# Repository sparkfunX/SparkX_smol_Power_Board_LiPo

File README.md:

# SparkX smôl Power Board : LiPo

[*SparkX smôl Power Board : LiPo (SPX-18622)*](https://www.sparkfun.com/products/18622)

A power board for smôl:
- LiPo battery connector and charger
- Fuel gauge
- ATtiny841 for intelligent power management

## Repository Contents

- **/Documentation** - Datasheets etc.
- **/Hardware** - Eagle design files
- **LICENSE.md** contains the licence information

## Product Versions

- [SPX-18622](https://www.sparkfun.com/products/18622) - Original SparkX Release.

## License Information

This product is _**open source**_!

Please review the LICENSE.md file for license information.

If you have any questions or concerns on licensing, please contact technical support on our [SparkFun forums](https://forum.sparkfun.com/viewforum.php?f=123).

Distributed as-is; no warranty is given.

- Your friends at SparkFun.

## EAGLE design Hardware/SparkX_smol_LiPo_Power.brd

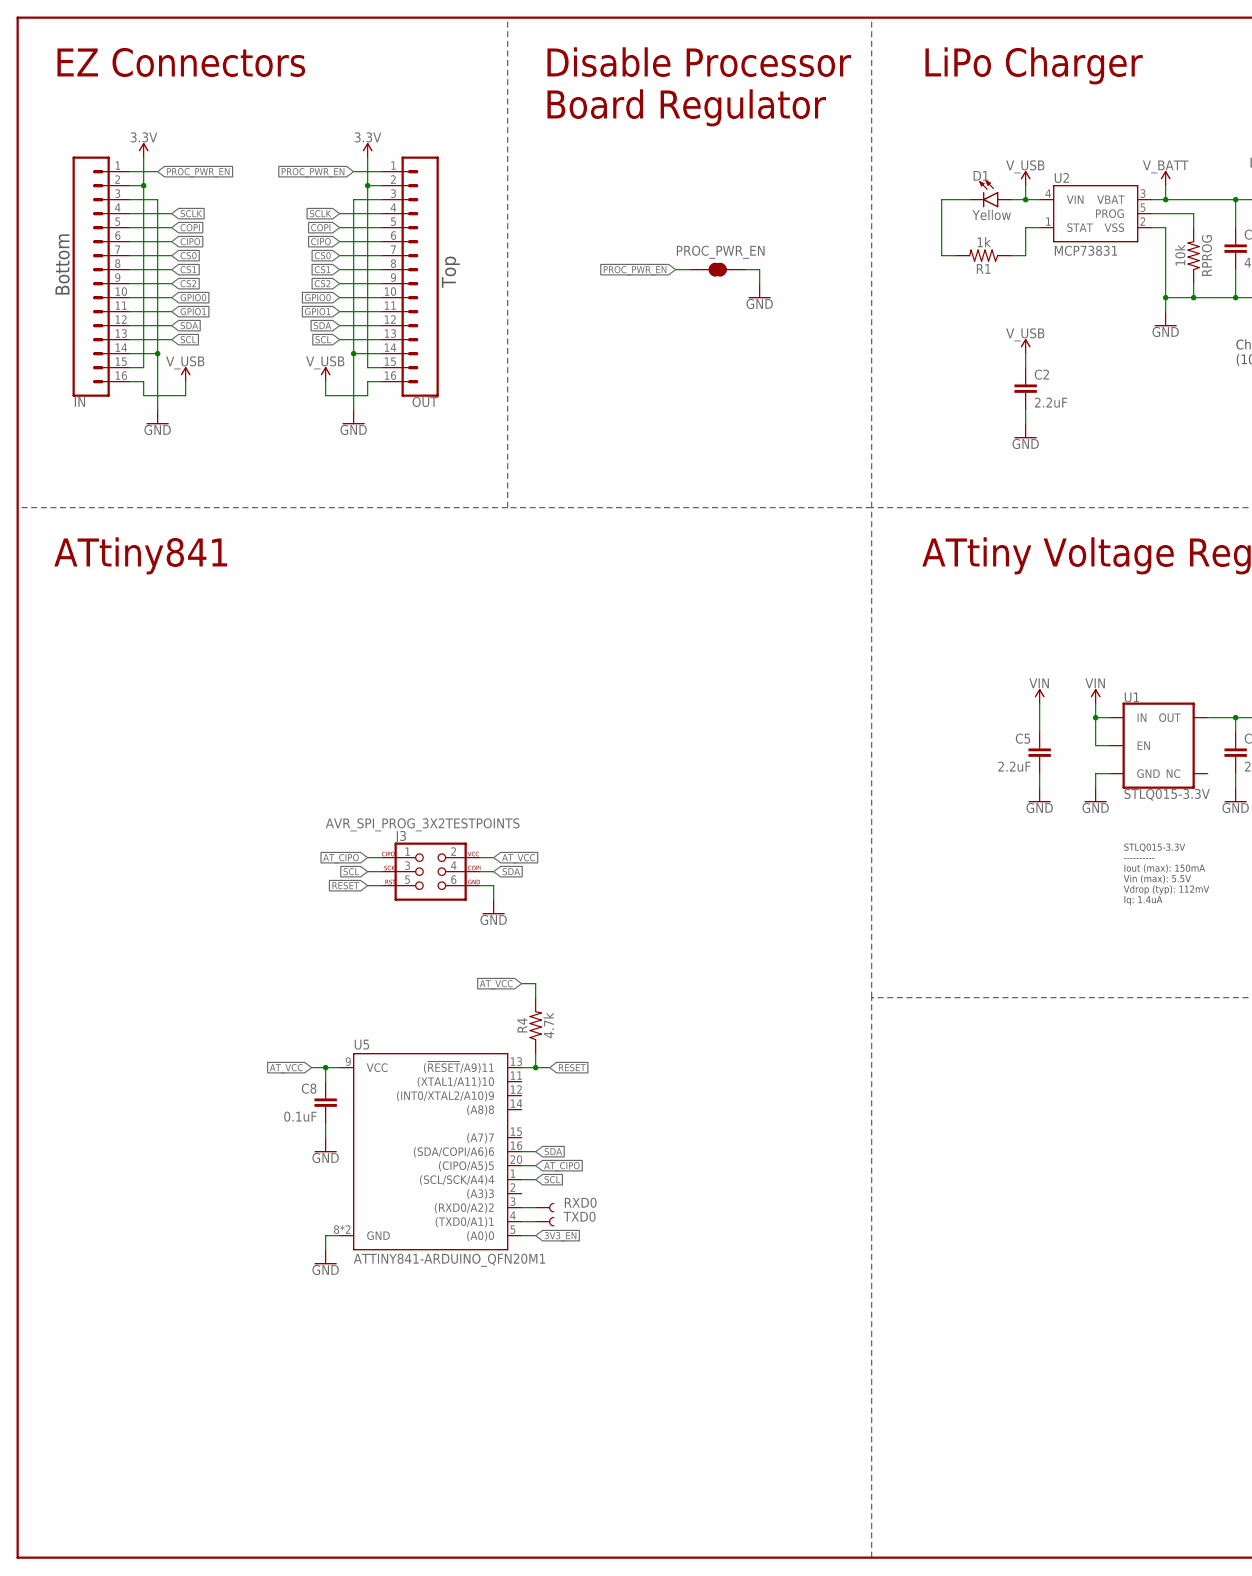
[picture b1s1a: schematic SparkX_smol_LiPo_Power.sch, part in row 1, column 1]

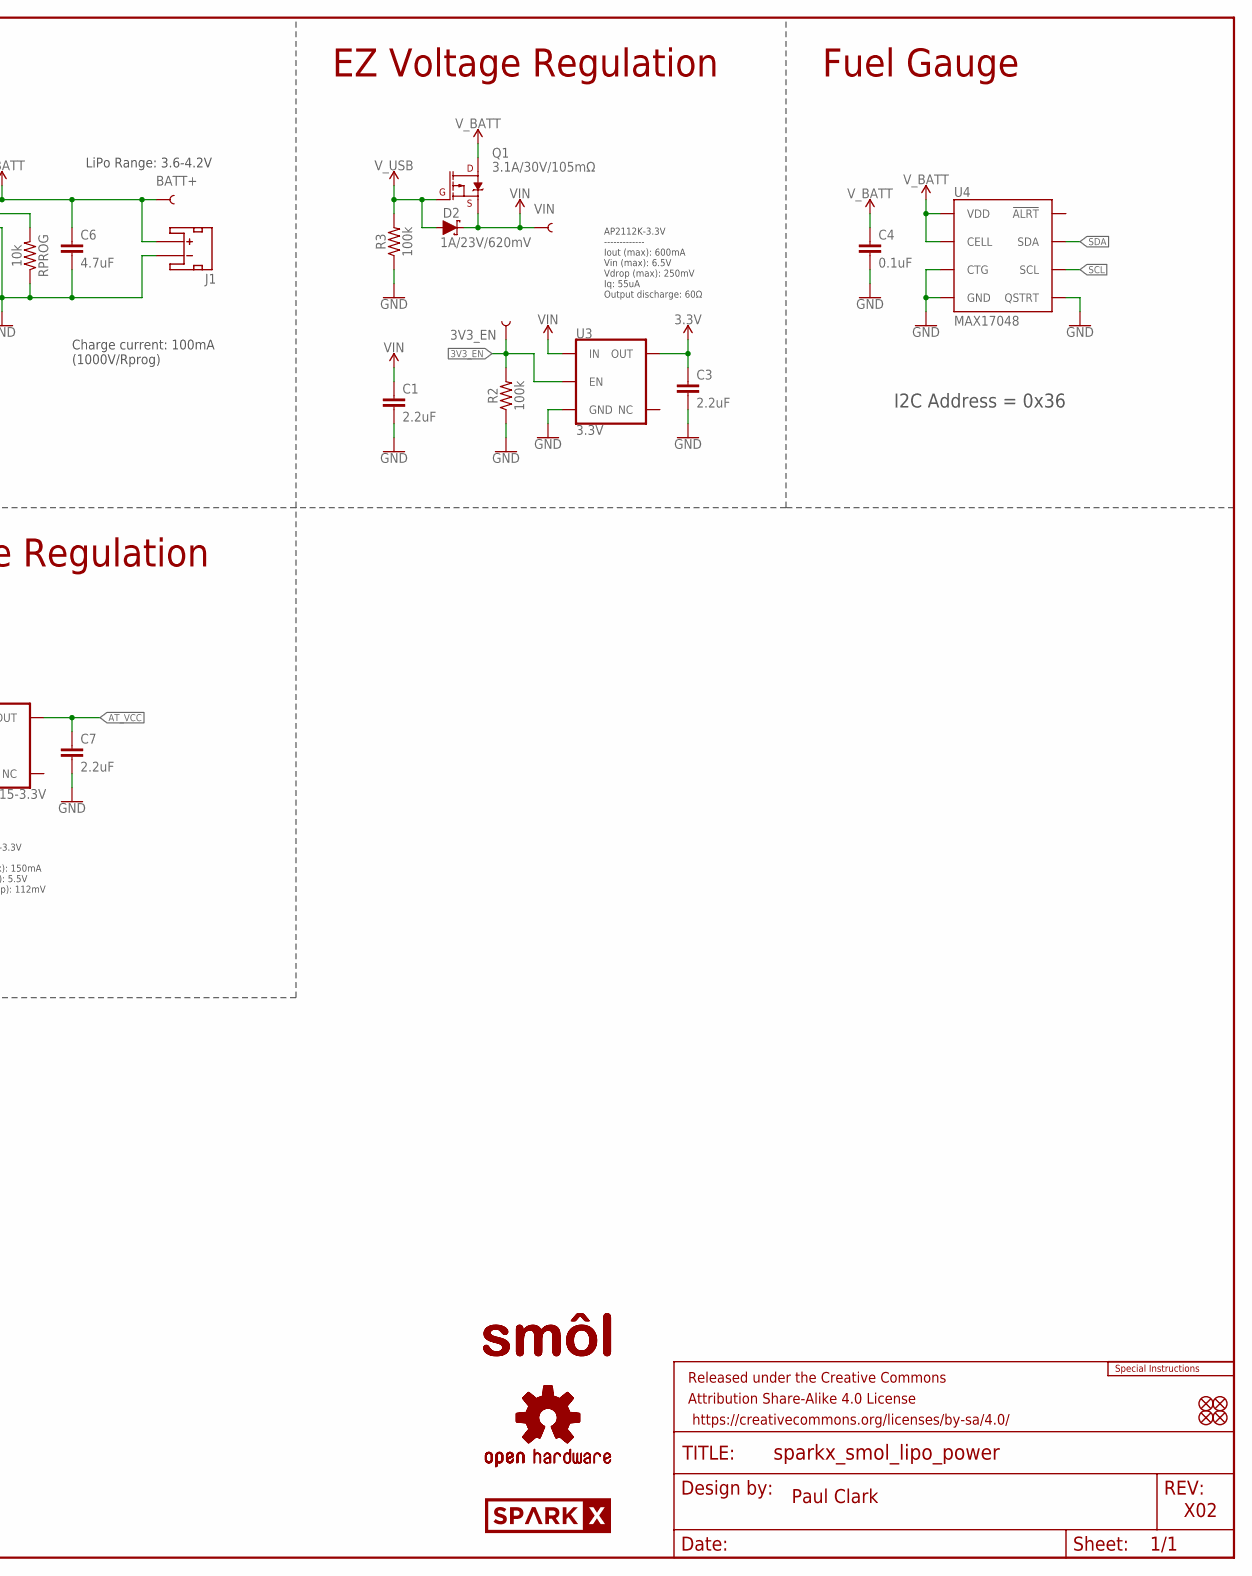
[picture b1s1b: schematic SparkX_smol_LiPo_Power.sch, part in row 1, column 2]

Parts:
3V3_EN: TEST-POINT3X4; PAD.03X.04
BATT+: TEST-POINT3X4; PAD.03X.04
C1, C2, C3, C5, C7: 2.2uF; 0402-TIGHT
C4, C8: 0.1uF; 0402-TIGHT
C6: 4.7uF; 0402-TIGHT
D1: Yellow; LED-0603
D2: 1A/23V/620mV; SOD-323
FD1, FD2, FD3, FD4: FIDUCIALUFIDUCIAL; FIDUCIAL-MICRO
FRAME1: FRAME-LEDGER; CREATIVE_COMMONS
IN: CONN_16FPC_16_0.5MM; FPC_16_0.5MM
J1: JST_2MM_MALE; JST-2-SMD
J3: AVR_SPI_PROG_3X2TESTPOINTS; 2X3_TEST_POINTS
LOGO1: SPECIAL_INSTRUCTIONS-ORDERING; ORDERING_INSTRUCTIONS
LOGO2, LOGO3: OSHW-LOGOMINI; OSHW-LOGO-MINI
OUT: CONN_16FPC_16_0.5MM; FPC_16_0.5MM
PROC_PWR_EN: JUMPER-SMT_2_NC_TRACE_SILK; SMT-JUMPER_2_NC_TRACE_SILK
Q1: 3.1A/30V/105mΩ; SOT23-3
R1: 1k; 0402-TIGHT
R2, R3: 100k; 0402-TIGHT
R4: 4.7k; 0402-TIGHT
RPROG: 10k; 0402-TIGHT
RXD0: TEST-POINT3X4; PAD.03X.04
TXD0: TEST-POINT3X4; PAD.03X.04
U1: STLQ015-3.3V; SOT23-5
U2: MCP73831; SOT23-5
U3: 3.3V; SOT23-5
U4: MAX17048; DFN-8
U5: ATTINY841-ARDUINO_QFN20M1; QFN20_20M1
U$1: SPARKX-LOGO3; SPARKX-SMALL
U$3, U$9: SMOL_LOGOSMALL; SMOL_SMALL
VIN: TEST-POINT3X4; PAD.03X.04

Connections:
3.3V: C3.1, IN.2, IN.15, OUT.2, OUT.15, U3.5 (OUT)
3V3_EN: 3V3_EN.1, R2.2, U3.3 (EN), U5.5 ((A0)0)
!RESET!: J3.5, R4.1, U5.13 ((!RESET!/A9)11)
AT_CIPO: J3.1, U5.20 ((CIPO/A5)5)
AT_VCC: C7.1, C8.1, J3.2, R4.2, U1.5 (OUT), U5.9 (VCC)
CHG_LED: R1.1, U2.1 (STAT)
CIPO: IN.6, OUT.6
COPI: IN.5, OUT.5
CS0: IN.7, OUT.7
CS1: IN.8, OUT.8
CS2: IN.9, OUT.9
GND: C1.2, C2.2, C3.2, C4.2, C5.2, C6.2, C7.2, C8.2, IN.3, IN.14, J1.1 (-), J3.6, OUT.3, OUT.14, PROC_PWR_EN.2, R2.1, R3.1, RPROG.1, U1.2 (GND), U2.2 (VSS), U3.2 (GND), U4.1 (CTG), U4.4 (GND), U4.6 (QSTRT), U4.9 (GND), U5.8 (GND), U5.PAD (GND)
GPIO0: IN.10, OUT.10
GPIO1: IN.11, OUT.11
unnamed: RPROG.2, U2.5 (PROG)
unnamed: D1.C, R1.2
PROC_PWR_EN: IN.1, OUT.1, PROC_PWR_EN.1
RXD0: RXD0.1, U5.3 ((RXD0/A2)2)
SCL: IN.13, J3.3, OUT.13, U4.7 (SCL), U5.1 ((SCL/SCK/A4)4)
SCLK: IN.4, OUT.4
SDA: IN.12, J3.4, OUT.12, U4.8 (SDA), U5.16 ((SDA/COPI/A6)6)
TXD0: TXD0.1, U5.4 ((TXD0/A1)1)
VIN: C1.1, C5.1, D2.C, Q1.2 (S), U1.1 (IN), U1.3 (EN), U3.1 (IN), VIN.1
V_BATT: BATT+.1, C4.1, C6.1, J1.2 (+), Q1.3 (D), U2.3 (VBAT), U4.2 (CELL), U4.3 (VDD)
V_USB: C2.1, D1.A, D2.A, IN.16, OUT.16, Q1.1 (G), R3.2, U2.4 (VIN)

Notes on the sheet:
Paul Clark
X02
EZ Connectors
Top
Bottom
LiPo Charger
LiPo Range: 3.6-4.2V
Charge current: 100mA (1000V/Rprog)
EZ Voltage Regulation
Disable Processor Board Regulator
AP2112K-3.3V ------------- Iout (max): 600mA Vin (max): 6.5V Vdrop (max): 250mV Iq: 55uA Output discharge: 60Ω
Fuel Gauge
I2C Address = 0x36
ATtiny841
STLQ015-3.3V ---------- Iout (max): 150mA Vin (max): 5.5V Vdrop (typ): 112mV Iq: 1.4uA
ATtiny Voltage Regulation

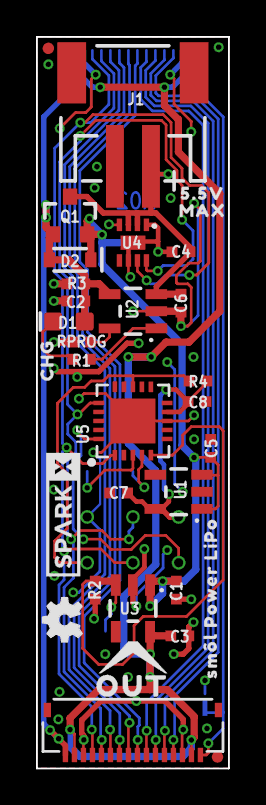
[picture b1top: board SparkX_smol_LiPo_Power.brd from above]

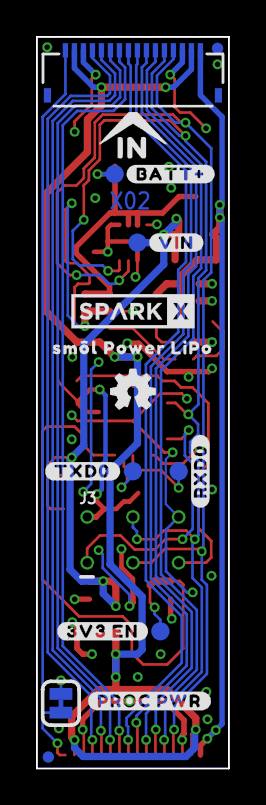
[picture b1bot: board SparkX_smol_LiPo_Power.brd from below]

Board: 2 copper layers, 10.7 x 40.6 mm, 56 parts (21 on the bottom side), 25 nets.

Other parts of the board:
U$2, U$18: SM�L_POWER_LIPO0
U$4: #BATT##0
U$5: #VIN#0
U$6: #3V3_EN#0
U$7: #PROC_PWR#0
U$8: IN0
U$10: CHG0
U$11: MAX0
U$14: #RXD0#0
U$15: #TXD0#0
U$16: 5#5V0
U$17: OUT0
U$20: SPARKX-LOGO3; SPARKX-SMALL

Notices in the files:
parts and their libraries:
SparkFun-Aesthetics: Licensing: Creative Commons ShareAlike 4.0 International - https://creativecommons.org/licenses/by-sa/4.0
SparkFun-Aesthetics: Released under the Creative Commons Attribution Share-Alike 4.0 License
SparkFun-Aesthetics: https://creativecommons.org/licenses/by-sa/4.0
